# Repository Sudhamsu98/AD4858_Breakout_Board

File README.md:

# AD4858_Breakout_Board
KiCAD board files for the AD4858 ADC chip breaking out each pin and revision control

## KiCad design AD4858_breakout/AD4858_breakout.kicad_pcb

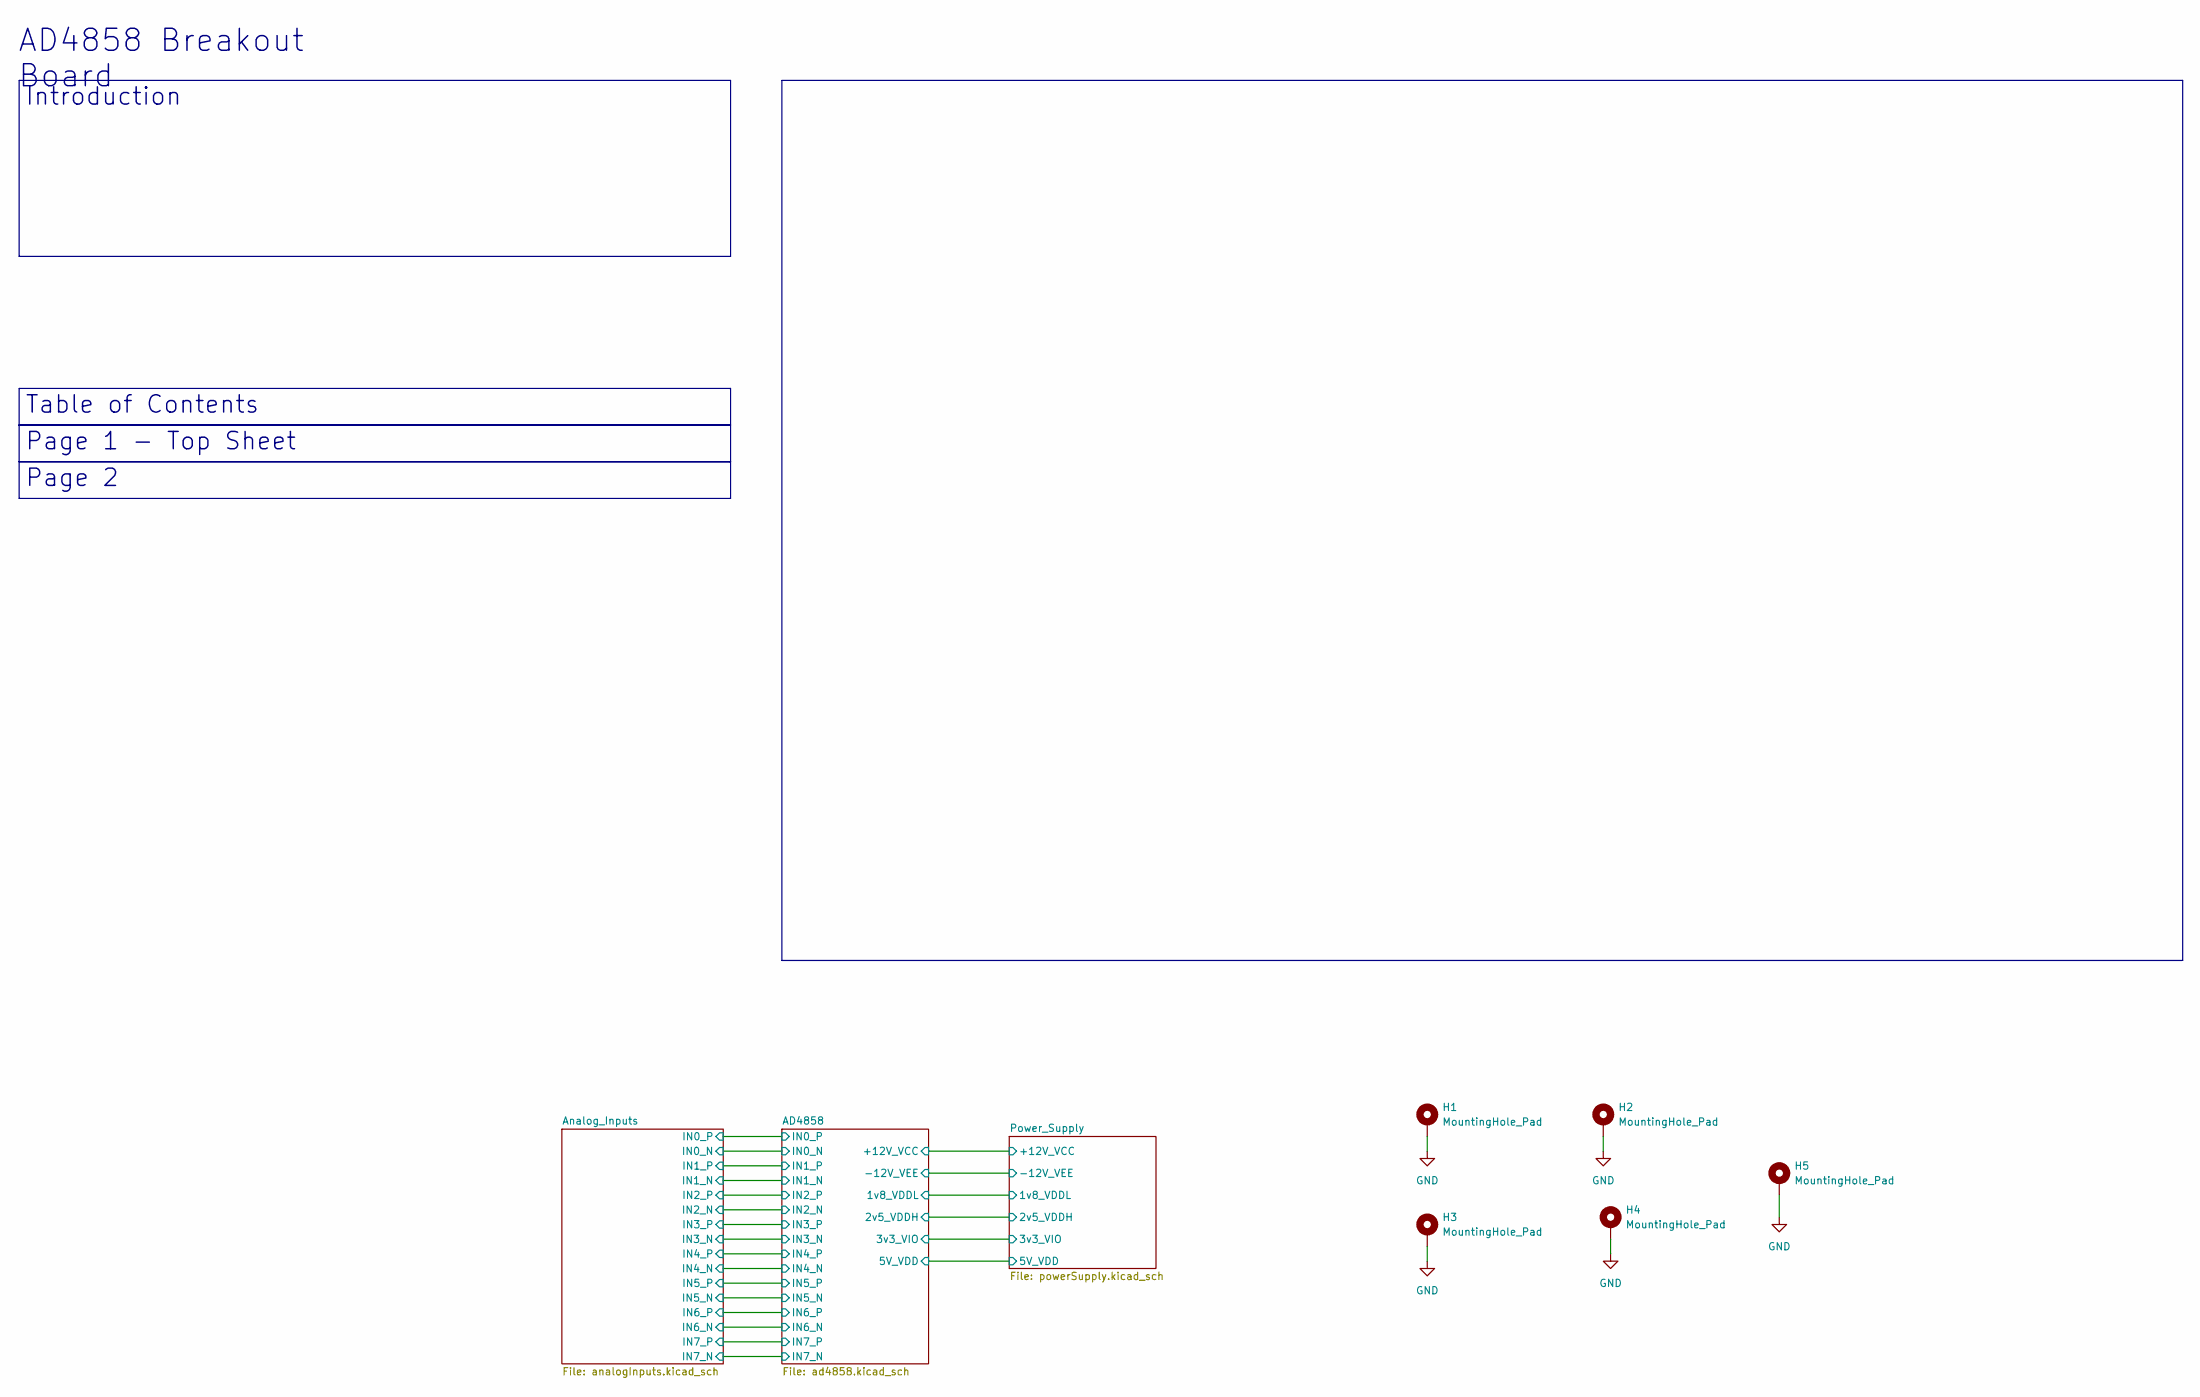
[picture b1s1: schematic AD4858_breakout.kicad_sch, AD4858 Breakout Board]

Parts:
H1, H2, H3, H4, H5: MountingHole_Pad; MountingHole_3.2mm_M3_DIN965_Pad

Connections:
GND: H1.1, H2.1, H3.1, H4.1, H5.1; also elsewhere on the board

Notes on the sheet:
Table of Contents
Page 1 - Top Sheet
Introduction
Page 2
AD4858 Breakout Board

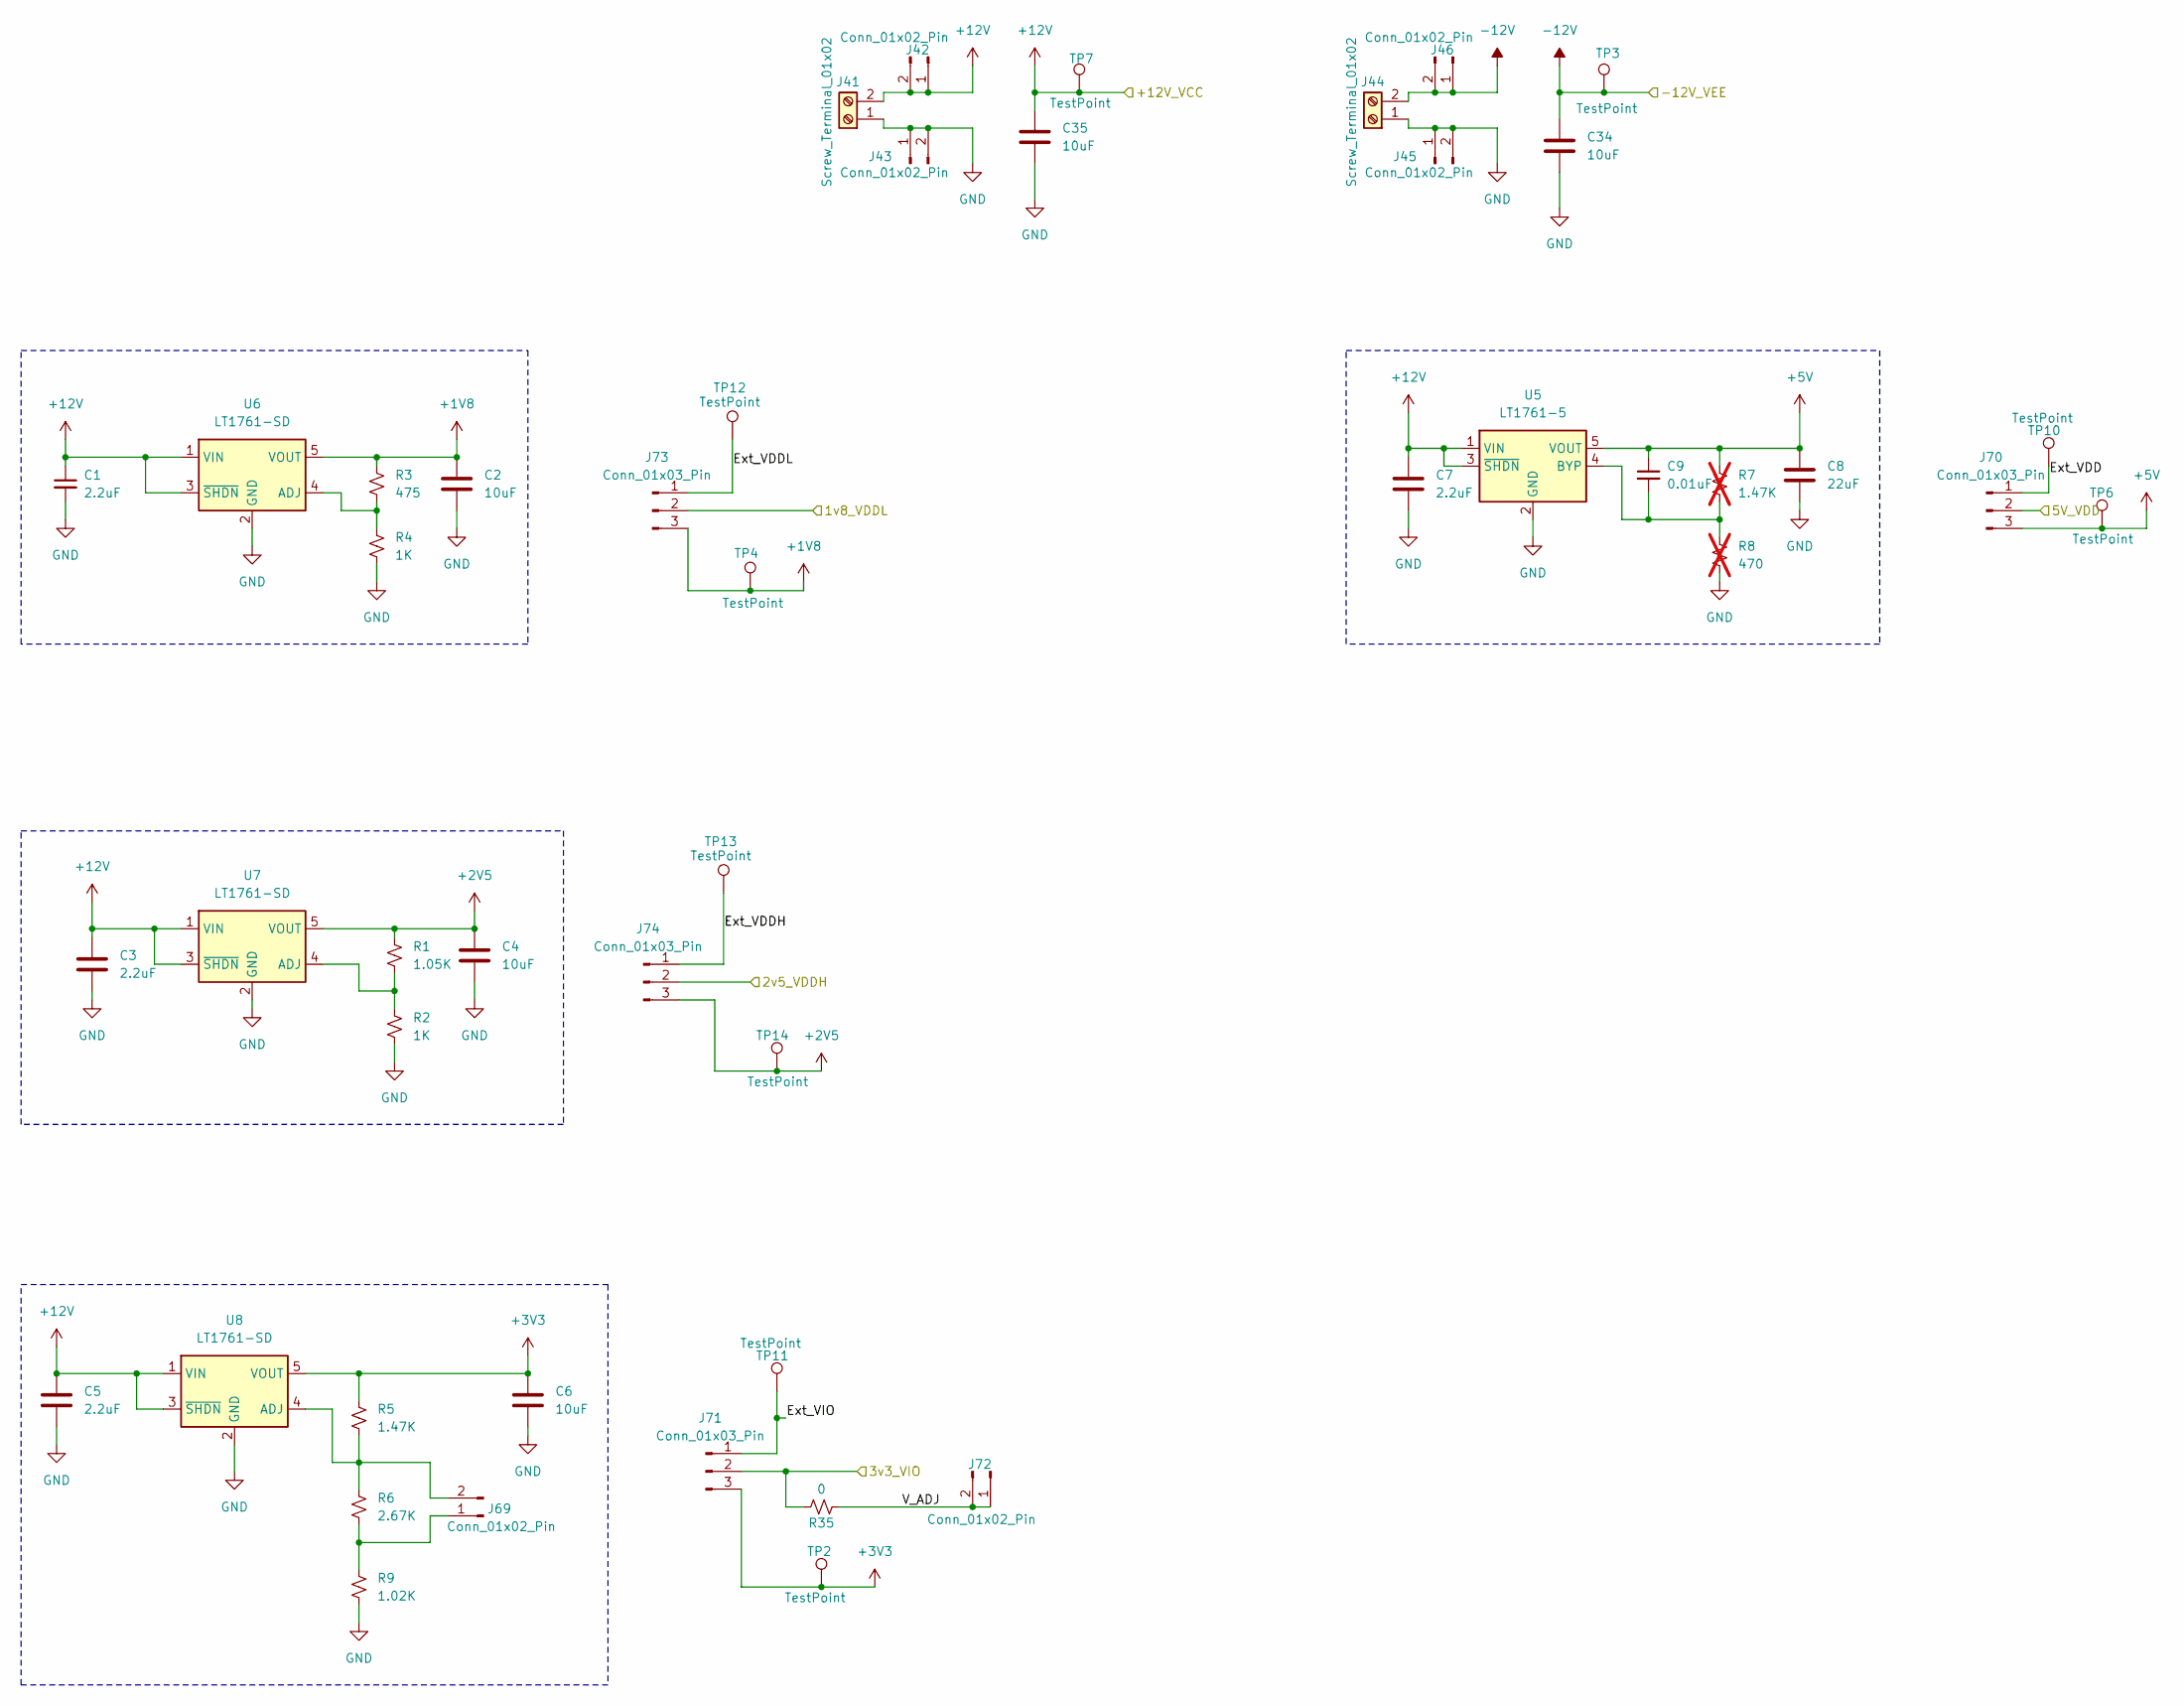
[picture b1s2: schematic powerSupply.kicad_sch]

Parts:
C1, C3, C5, C7: 2.2uF; C_0603_1608Metric
C2, C4, C6, C34, C35: 10uF; C_0805_2012Metric
C8: 22uF; C_0805_2012Metric
C9: 0.01uF; C_0603_1608Metric
J41, J44: Screw_Terminal_01x02; TerminalBlock_Phoenix_PT-1,5-2-3.5-H_1x02_P3.50mm_Horizontal
J42, J43, J45, J46, J69, J72: Conn_01x02_Pin; PinHeader_1x02_P2.54mm_Vertical
J70, J71, J73, J74: Conn_01x03_Pin; PinHeader_1x03_P2.54mm_Vertical
R1: 1.05K; R_0603_1608Metric
R2, R4: 1K; R_0603_1608Metric
R3: 475; R_0603_1608Metric
R5: 1.47K; R_0603_1608Metric
R6: 2.67K; R_0603_1608Metric
R7: 1.47K; R_0603_1608Metric; not fitted
R8: 470; R_0603_1608Metric; not fitted
R9: 1.02K; R_0603_1608Metric
R35: 0; R_0603_1608Metric
TP2, TP3, TP4, TP6, TP7, TP10, TP11, TP12, TP13, TP14: TestPoint; TestPoint_Pad_D1.0mm
U5: LT1761-5; TSOT-23-5
U6, U7, U8: LT1761-SD; TSOT-23-5

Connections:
+1V8: C2.1, J73.3, R3.1, TP4.1, U6.5 (VOUT)
+2V5: C4.1, J74.3, R1.1, TP14.1, U7.5 (VOUT)
+3V3: C6.1, J71.3, R5.1, TP2.1, U8.5 (VOUT)
+5V: C8.1, C9.1, J70.3, R7.1, TP6.1, U5.5 (VOUT)
+12V: C1.1, C3.1, C5.1, C7.1, C35.1, J41.2, J42.1, J42.2, TP7.1, U5.1 (VIN), U5.3 (~SHDN), U6.1 (VIN), U6.3 (~SHDN), U7.1 (VIN), U7.3 (~SHDN), U8.1 (VIN), U8.3 (~SHDN); also elsewhere on the board
-12V: C34.1, J44.2, J46.1, J46.2, TP3.1; also elsewhere on the board
/AD4858/1v8_VDDL: J73.2; also elsewhere on the board
/AD4858/2v5_VDDH: J74.2; also elsewhere on the board
/AD4858/3v3_VIO: J71.2, R35.2; also elsewhere on the board
/AD4858/5V_VDD: J70.2; also elsewhere on the board
/Power_Supply/Ext_VDD: J70.1, TP10.1
/Power_Supply/Ext_VDDH: J74.1, TP13.1
/Power_Supply/Ext_VDDL: J73.1, TP12.1
/Power_Supply/Ext_VIO: J71.1, TP11.1
/Power_Supply/V_ADJ: J72.1, J72.2, R35.1
GND: C1.2, C2.2, C3.2, C4.2, C5.2, C6.2, C7.2, C8.2, C34.2, C35.2, J41.1, J43.1, J43.2, J44.1, J45.1, J45.2, R2.2, R4.2, R8.2, R9.2, U5.2 (GND), U6.2 (GND), U7.2 (GND), U8.2 (GND); also elsewhere on the board
unnamed: J69.1, R6.2, R9.1
unnamed: J69.2, R5.2, R6.1, U8.4 (ADJ)
unnamed: C9.2, R7.2, R8.1, U5.4 (BYP)
unnamed: R3.2, R4.1, U6.4 (ADJ)
unnamed: R1.2, R2.1, U7.4 (ADJ)

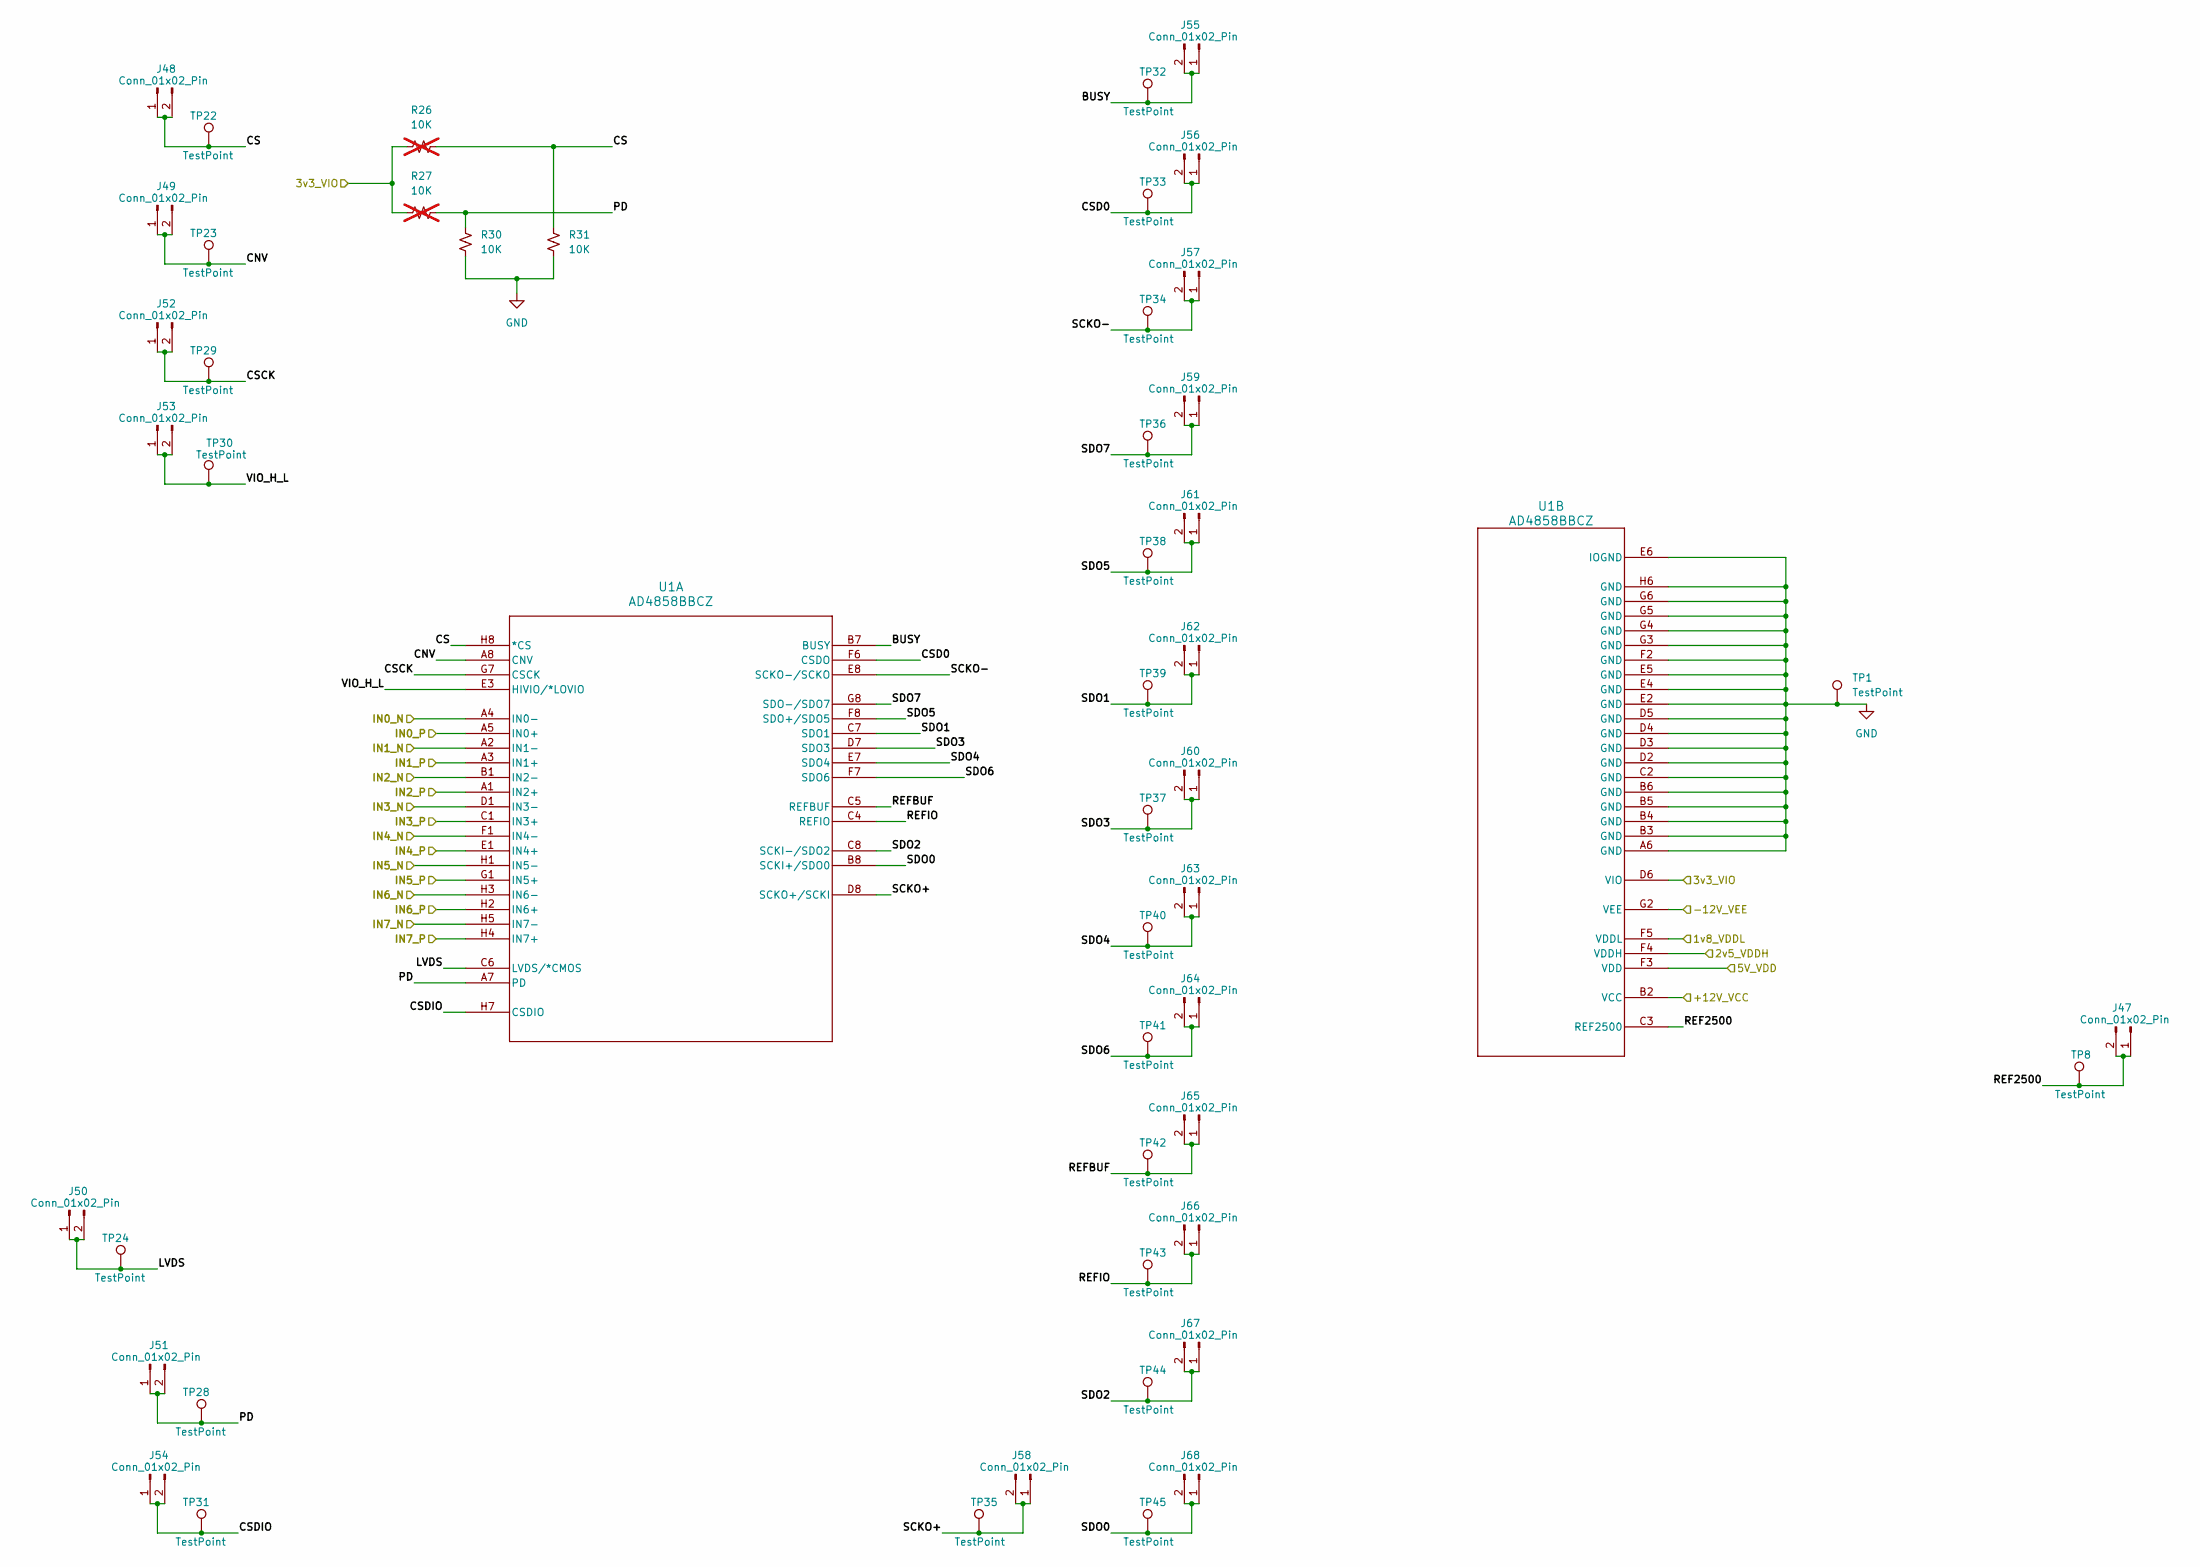
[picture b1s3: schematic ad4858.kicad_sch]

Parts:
J47, J48, J49, J50, J51, J52, J53, J54, J55, J56, J57, J58, J59, J60, J61, J62, J63, J64, J65, J66, J67, J68: Conn_01x02_Pin; PinHeader_1x02_P2.54mm_Vertical
R26, R27: 10K; R_0603_1608Metric; not fitted
R30, R31: 10K; R_0603_1608Metric
TP1, TP8, TP22, TP23, TP24, TP28, TP29, TP30, TP31, TP32, TP33, TP34, TP35, TP36, TP37, TP38, TP39, TP40, TP41, TP42, TP43, TP44, TP45: TestPoint; TestPoint_Pad_D1.0mm
U1: AD4858BBCZ; BGA-64_05-08-7086_ADI

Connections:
+12V: U1.B2 (VCC); also elsewhere on the board
-12V: U1.G2 (VEE); also elsewhere on the board
/AD4858/1v8_VDDL: U1.F5 (VDDL); also elsewhere on the board
/AD4858/2v5_VDDH: U1.F4 (VDDH); also elsewhere on the board
/AD4858/3v3_VIO: R26.1, R27.1, U1.D6 (VIO); also elsewhere on the board
/AD4858/5V_VDD: U1.F3 (VDD); also elsewhere on the board
/AD4858/BUSY: J55.1, J55.2, TP32.1, U1.B7 (BUSY)
/AD4858/CNV: J49.1, J49.2, TP23.1, U1.A8 (CNV)
/AD4858/CS: J48.1, J48.2, R26.2, R31.2, TP22.1, U1.H8 (*CS)
/AD4858/CSCK: J52.1, J52.2, TP29.1, U1.G7 (CSCK)
/AD4858/CSD0: J56.1, J56.2, TP33.1, U1.F6 (CSDO)
/AD4858/CSDIO: J54.1, J54.2, TP31.1, U1.H7 (CSDIO)
/AD4858/IN0_N: U1.A4 (IN0-); also elsewhere on the board
/AD4858/IN0_P: U1.A5 (IN0+); also elsewhere on the board
/AD4858/IN1_N: U1.A2 (IN1-); also elsewhere on the board
/AD4858/IN1_P: U1.A3 (IN1+); also elsewhere on the board
/AD4858/IN2_N: U1.B1 (IN2-); also elsewhere on the board
/AD4858/IN2_P: U1.A1 (IN2+); also elsewhere on the board
/AD4858/IN3_N: U1.D1 (IN3-); also elsewhere on the board
/AD4858/IN3_P: U1.C1 (IN3+); also elsewhere on the board
/AD4858/IN4_N: U1.F1 (IN4-); also elsewhere on the board
/AD4858/IN4_P: U1.E1 (IN4+); also elsewhere on the board
/AD4858/IN5_N: U1.H1 (IN5-); also elsewhere on the board
/AD4858/IN5_P: U1.G1 (IN5+); also elsewhere on the board
/AD4858/IN6_N: U1.H3 (IN6-); also elsewhere on the board
/AD4858/IN6_P: U1.H2 (IN6+); also elsewhere on the board
/AD4858/IN7_N: U1.H5 (IN7-); also elsewhere on the board
/AD4858/IN7_P: U1.H4 (IN7+); also elsewhere on the board
/AD4858/LVDS: J50.1, J50.2, TP24.1, U1.C6 (LVDS/*CMOS)
/AD4858/PD: J51.1, J51.2, R27.2, R30.2, TP28.1, U1.A7 (PD)
/AD4858/REF2500: J47.1, J47.2, TP8.1, U1.C3 (REF2500)
/AD4858/REFBUF: J65.1, J65.2, TP42.1, U1.C5 (REFBUF)
/AD4858/REFIO: J66.1, J66.2, TP43.1, U1.C4 (REFIO)
/AD4858/SCKO+: J58.1, J58.2, TP35.1, U1.D8 (SCKO+/SCKI)
/AD4858/SCKO-: J57.1, J57.2, TP34.1, U1.E8 (SCKO-/SCKO)
/AD4858/SDO0: J68.1, J68.2, TP45.1, U1.B8 (SCKI+/SDO0)
/AD4858/SDO1: J62.1, J62.2, TP39.1, U1.C7 (SDO1)
/AD4858/SDO2: J67.1, J67.2, TP44.1, U1.C8 (SCKI-/SDO2)
/AD4858/SDO3: J60.1, J60.2, TP37.1, U1.D7 (SDO3)
/AD4858/SDO4: J63.1, J63.2, TP40.1, U1.E7 (SDO4)
/AD4858/SDO5: J61.1, J61.2, TP38.1, U1.F8 (SDO+/SDO5)
/AD4858/SDO6: J64.1, J64.2, TP41.1, U1.F7 (SDO6)
/AD4858/SDO7: J59.1, J59.2, TP36.1, U1.G8 (SDO-/SDO7)
/AD4858/VIO_H_L: J53.1, J53.2, TP30.1, U1.E3 (HIVIO/*LOVIO)
GND: R30.1, R31.1, TP1.1, U1.A6 (GND), U1.B3 (GND), U1.B4 (GND), U1.B5 (GND), U1.B6 (GND), U1.C2 (GND), U1.D2 (GND), U1.D3 (GND), U1.D4 (GND), U1.D5 (GND), U1.E2 (GND), U1.E4 (GND), U1.E5 (GND), U1.E6 (IOGND), U1.F2 (GND), U1.G3 (GND), U1.G4 (GND), U1.G5 (GND), U1.G6 (GND), U1.H6 (GND); also elsewhere on the board

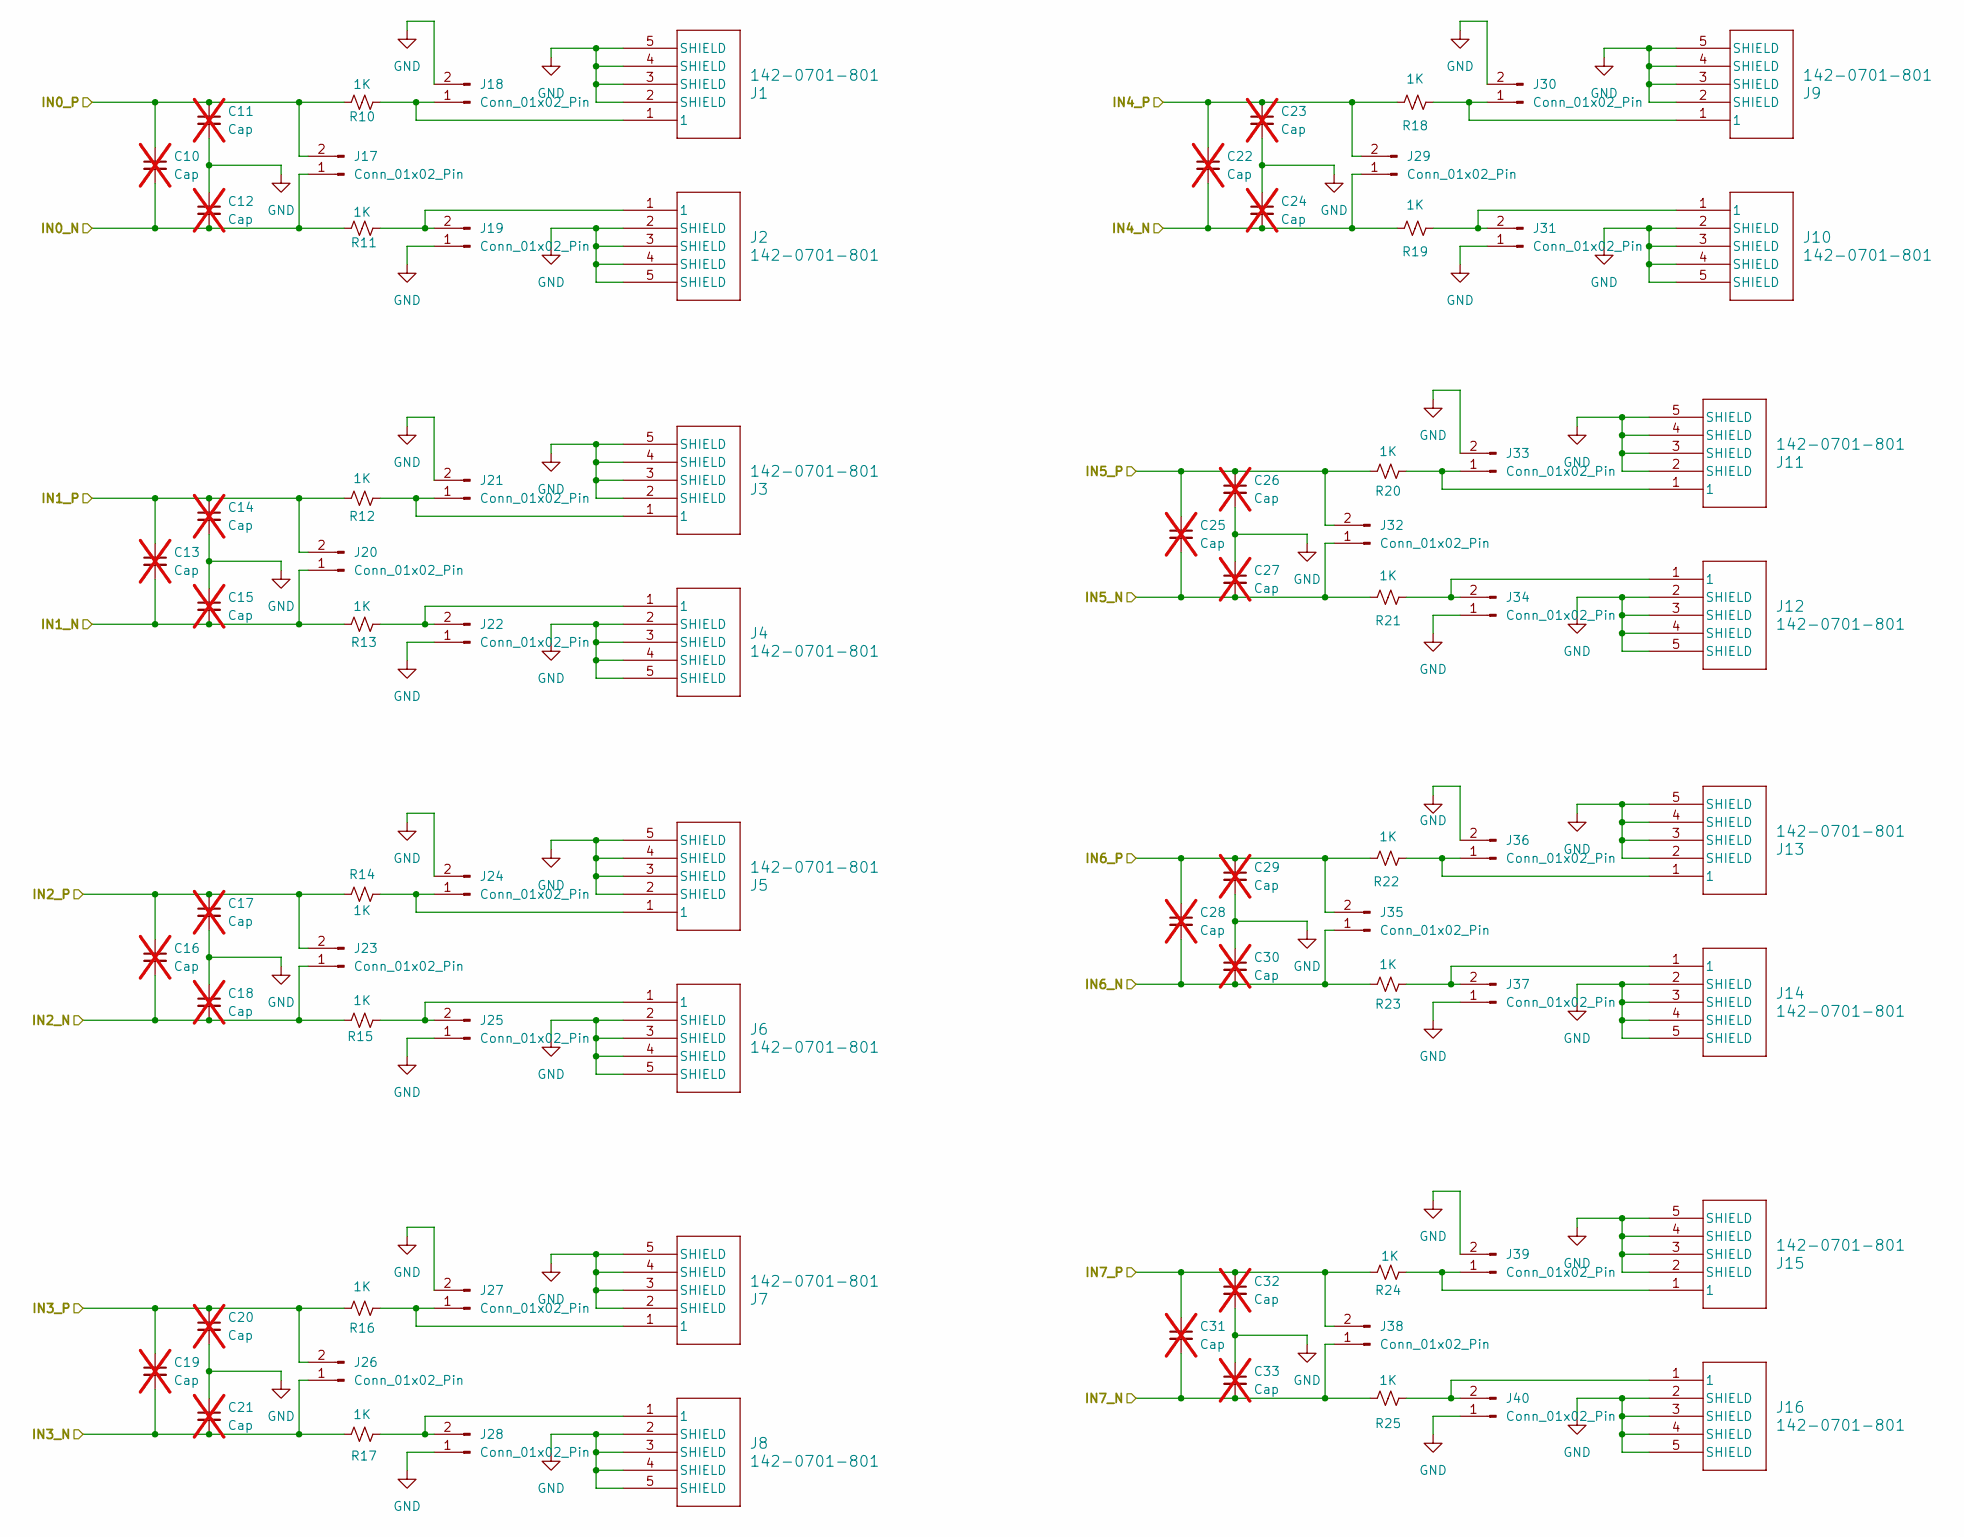
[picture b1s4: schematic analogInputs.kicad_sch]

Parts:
C10, C11, C12, C13, C14, C15, C16, C17, C18, C19, C20, C21, C22, C23, C24, C25, C26, C27, C28, C29, C30, C31, C32, C33: Cap; C_0603_1608Metric; not fitted
J1, J2, J3, J4, J5, J6, J7, J8, J9, J10, J11, J12, J13, J14, J15, J16: 142-0701-801; CONN_142-0701-801
J17, J18, J19, J20, J21, J22, J23, J24, J25, J26, J27, J28, J29, J30, J31, J32, J33, J34, J35, J36, J37, J38, J39, J40: Conn_01x02_Pin; PinHeader_1x02_P2.54mm_Vertical
R10, R11, R12, R13, R14, R15, R16, R17, R18, R19, R20, R21, R22, R23, R24, R25: 1K; R_0603_1608Metric

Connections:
/AD4858/IN0_N: C10.2, C12.2, J17.1, R11.1; also elsewhere on the board
/AD4858/IN0_P: C10.1, C11.1, J17.2, R10.1; also elsewhere on the board
/AD4858/IN1_N: C13.2, C15.2, J20.1, R13.1; also elsewhere on the board
/AD4858/IN1_P: C13.1, C14.1, J20.2, R12.1; also elsewhere on the board
/AD4858/IN2_N: C16.2, C18.2, J23.1, R15.1; also elsewhere on the board
/AD4858/IN2_P: C16.1, C17.1, J23.2, R14.1; also elsewhere on the board
/AD4858/IN3_N: C19.2, C21.2, J26.1, R17.1; also elsewhere on the board
/AD4858/IN3_P: C19.1, C20.1, J26.2, R16.1; also elsewhere on the board
/AD4858/IN4_N: C22.2, C24.2, J29.1, R19.1; also elsewhere on the board
/AD4858/IN4_P: C22.1, C23.1, J29.2, R18.1; also elsewhere on the board
/AD4858/IN5_N: C25.2, C27.2, J32.1, R21.1; also elsewhere on the board
/AD4858/IN5_P: C25.1, C26.1, J32.2, R20.1; also elsewhere on the board
/AD4858/IN6_N: C28.2, C30.2, J35.1, R23.1; also elsewhere on the board
/AD4858/IN6_P: C28.1, C29.1, J35.2, R22.1; also elsewhere on the board
/AD4858/IN7_N: C31.2, C33.2, J38.1, R25.1; also elsewhere on the board
/AD4858/IN7_P: C31.1, C32.1, J38.2, R24.1; also elsewhere on the board
GND: C11.2, C12.1, C14.2, C15.1, C17.2, C18.1, C20.2, C21.1, C23.2, C24.1, C26.2, C27.1, C29.2, C30.1, C32.2, C33.1, J1.2 (SHIELD), J1.3 (SHIELD), J1.4 (SHIELD), J1.5 (SHIELD), J2.2 (SHIELD), J2.3 (SHIELD), J2.4 (SHIELD), J2.5 (SHIELD), J3.2 (SHIELD), J3.3 (SHIELD), J3.4 (SHIELD), J3.5 (SHIELD), J4.2 (SHIELD), J4.3 (SHIELD), J4.4 (SHIELD), J4.5 (SHIELD), J5.2 (SHIELD), J5.3 (SHIELD), J5.4 (SHIELD), J5.5 (SHIELD), J6.2 (SHIELD), J6.3 (SHIELD), J6.4 (SHIELD), J6.5 (SHIELD), J7.2 (SHIELD), J7.3 (SHIELD), J7.4 (SHIELD), J7.5 (SHIELD), J8.2 (SHIELD), J8.3 (SHIELD), J8.4 (SHIELD), J8.5 (SHIELD), J9.2 (SHIELD), J9.3 (SHIELD), J9.4 (SHIELD), J9.5 (SHIELD), J10.2 (SHIELD), J10.3 (SHIELD), J10.4 (SHIELD), J10.5 (SHIELD), J11.2 (SHIELD), J11.3 (SHIELD), J11.4 (SHIELD), J11.5 (SHIELD), J12.2 (SHIELD), J12.3 (SHIELD), J12.4 (SHIELD), J12.5 (SHIELD), J13.2 (SHIELD), J13.3 (SHIELD), J13.4 (SHIELD), J13.5 (SHIELD), J14.2 (SHIELD), J14.3 (SHIELD), J14.4 (SHIELD), J14.5 (SHIELD), J15.2 (SHIELD), J15.3 (SHIELD), J15.4 (SHIELD), J15.5 (SHIELD), J16.2 (SHIELD), J16.3 (SHIELD), J16.4 (SHIELD), J16.5 (SHIELD), J18.2, J19.1, J21.2, J22.1, J24.2, J25.1, J27.2, J28.1, J30.2, J31.1, J33.2, J34.1, J36.2, J37.1, J39.2, J40.1; also elsewhere on the board
unnamed: J1.1, J18.1, R10.2
unnamed: J2.1, J19.2, R11.2
unnamed: J3.1, J21.1, R12.2
unnamed: J4.1, J22.2, R13.2
unnamed: J5.1, J24.1, R14.2
unnamed: J6.1, J25.2, R15.2
unnamed: J7.1, J27.1, R16.2
unnamed: J8.1, J28.2, R17.2
unnamed: J9.1, J30.1, R18.2
unnamed: J10.1, J31.2, R19.2
unnamed: J11.1, J33.1, R20.2
unnamed: J12.1, J34.2, R21.2
unnamed: J13.1, J36.1, R22.2
unnamed: J14.1, J37.2, R23.2
unnamed: J15.1, J39.1, R24.2
unnamed: J16.1, J40.2, R25.2

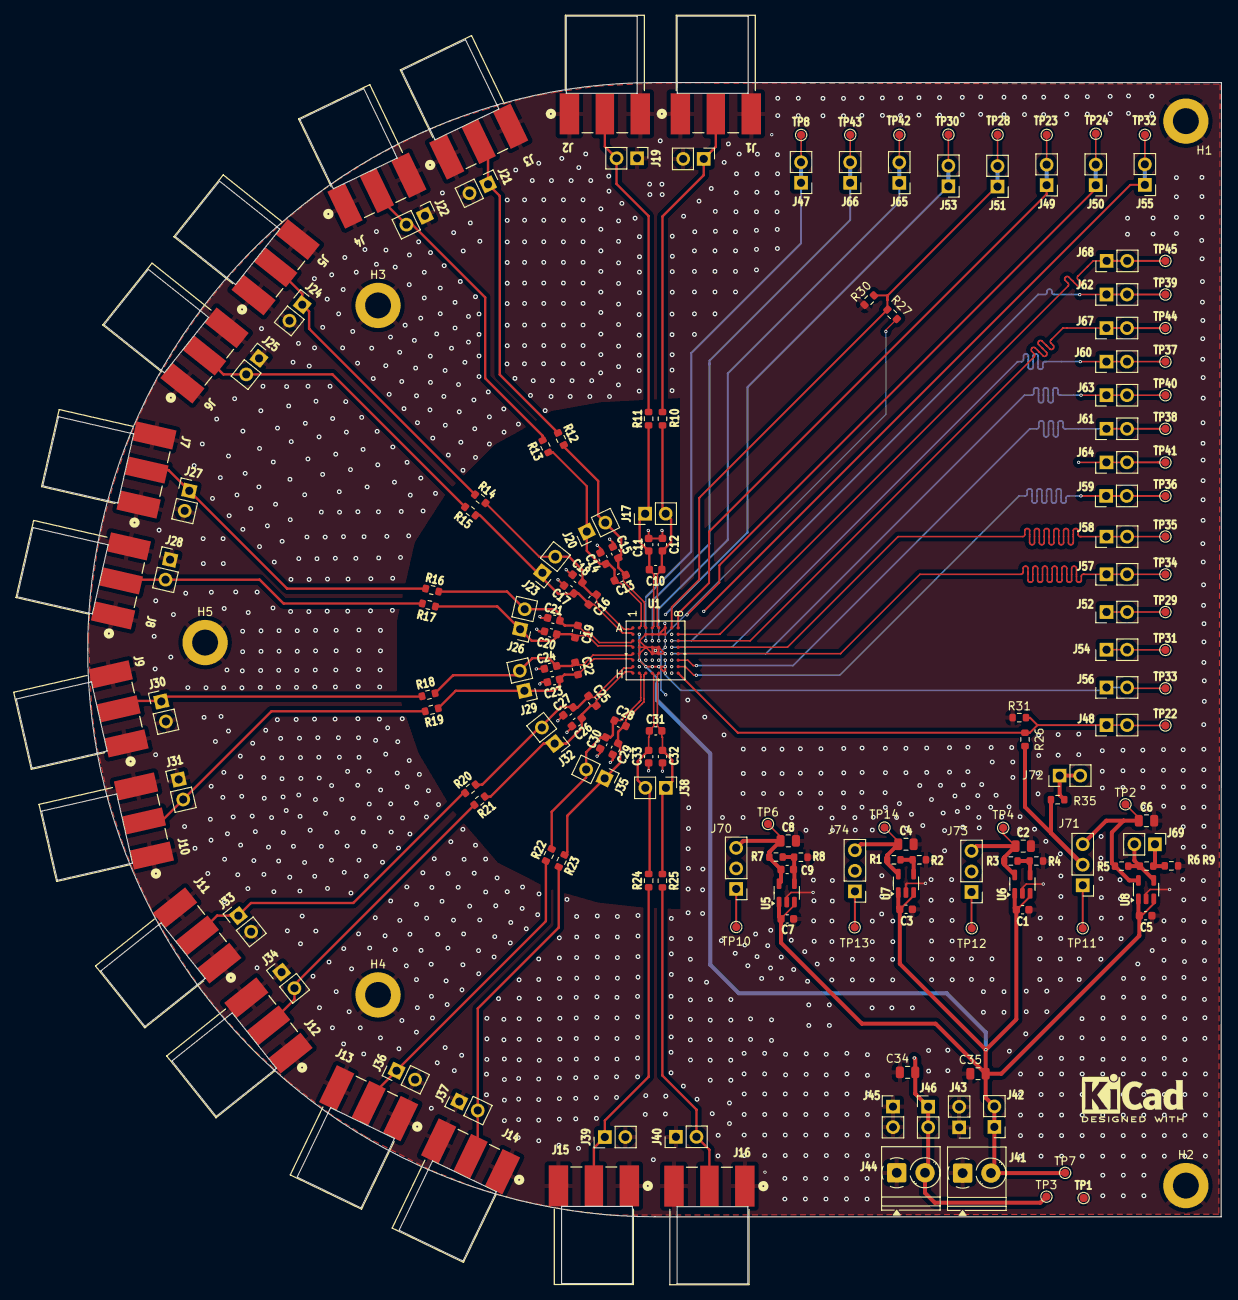
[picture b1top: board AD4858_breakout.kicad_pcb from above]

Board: 4 copper layers, 140.2 x 140.2 mm, 182 parts (0 on the bottom side), 75 nets.

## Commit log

2025-04-15 Added the KiCAD files in folders AD4858_breakout and Project_Libraries with completed initial board
2025-04-29 Updated the PCB file with length matched SD_lines and stiched ground
2025-04-29 made all the vias to blind/buried which were missed out
